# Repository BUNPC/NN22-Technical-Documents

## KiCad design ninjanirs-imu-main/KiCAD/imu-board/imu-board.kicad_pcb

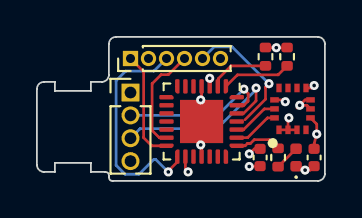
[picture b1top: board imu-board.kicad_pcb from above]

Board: 4 copper layers, 16.0 x 8.0 mm, 10 parts (0 on the bottom side), 14 nets.

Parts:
C1, C2: C_Small; C_0402_1005Metric
D1: LED; LED_0402_1005Metric
J1: Conn_01x04; PinHeader_1x04_P1.27mm_Vertical
J3: AVR-ISP-6; PinHeader_1x06_P1.00mm_Vertical
JP1, JP2: JPR2; R_0402_1005Metric
R1: R_US; R_0402_1005Metric
U2: ISM330DHCX; LGA-14L
U3: ATmega168A-MM; QFN-28-1EP_4x4mm_P0.45mm_EP2.4x2.4mm

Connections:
/MISO: J3.1 (MISO), U3.14 (PB4)
/MOSI: J3.4 (MOSI), U3.13 (PB3)
/RXD: J1.3, U3.26 (PD0)
/SCK: J3.3 (SCK), U3.15 (PB5)
/SCL: U2.P13 (SCL), U3.24 (PC5)
/SDA: U2.P14 (SDA/SDI/SDO), U3.23 (PC4)
/TXD: J1.2, U3.27 (PD1)
/nRESET: J3.5 (~RST), U3.25 (~RESET/PC6)
GND: C1.2, C2.2, D1.1 (K), J1.4, J3.6 (GND), JP1.2 (B), JP2.2 (B), U2.P1 (SDO/SA0), U2.P2 (SDX), U2.P3 (SCX), U2.P6 (GND@6), U2.P7 (GND@7), U3.4 (GND), U3.18 (GND), U3.29 (GND)
unnamed: D1.2 (A), R1.2
unnamed: JP1.1 (A), U3.2 (PD4)
unnamed: JP2.1 (A), U3.1 (PD3)
unnamed: R1.1, U3.22 (PC3)
VCC: C1.1, C2.1, J1.1, J3.2 (VCC), U2.P5 (VDD_IO), U2.P8 (VDD), U2.P12 (~CS), U3.3 (VCC), U3.16 (AVCC)

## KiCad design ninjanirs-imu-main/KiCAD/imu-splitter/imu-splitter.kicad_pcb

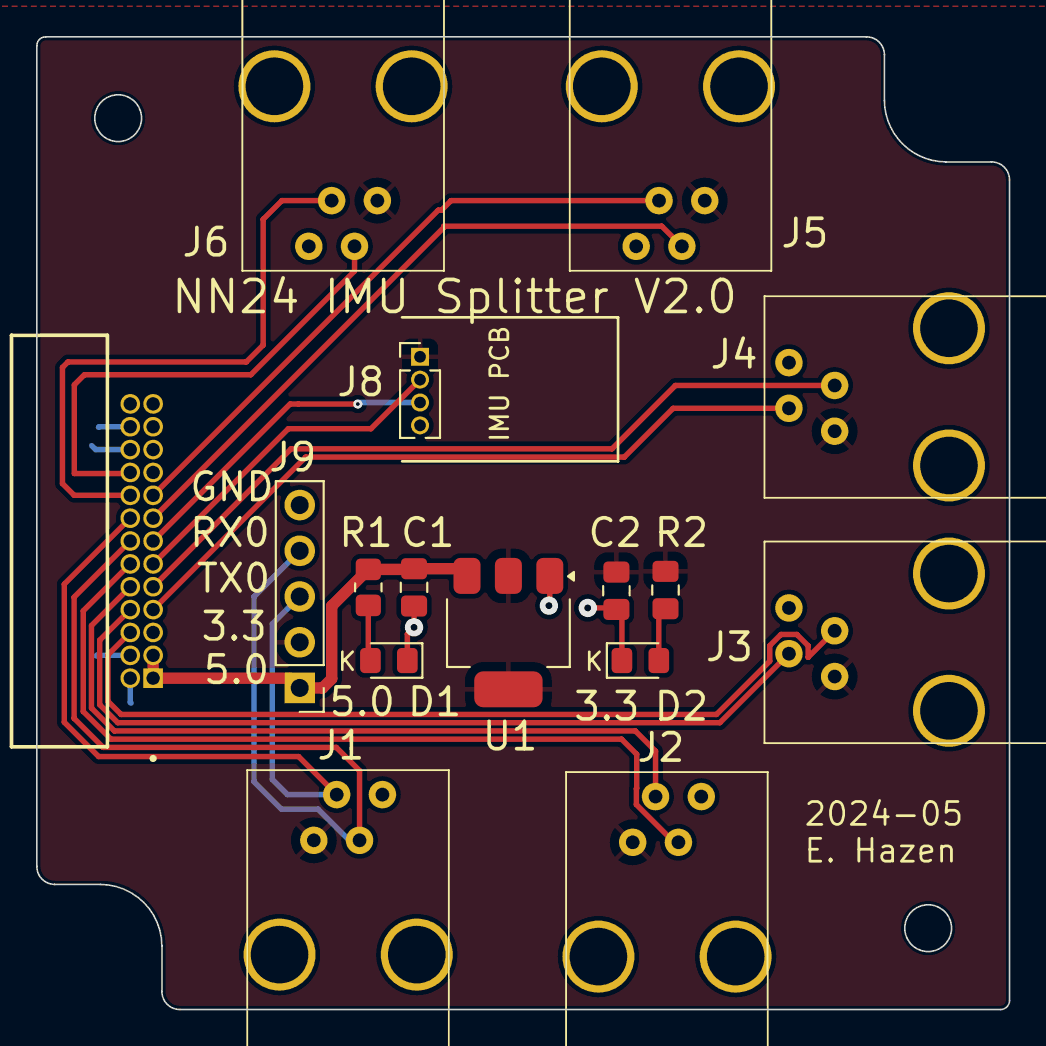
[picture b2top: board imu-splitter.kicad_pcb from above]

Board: 2 copper layers, 54.0 x 54.0 mm, 16 parts (0 on the bottom side), 19 nets.

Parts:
C1: 10uF; C_0805_2012Metric_Pad1.18x1.45mm_HandSolder
C2: 22uF; C_0805_2012Metric_Pad1.18x1.45mm_HandSolder
D1, D2: LED; LED_0805_2012Metric_Pad1.15x1.40mm_HandSolder
J1, J2, J3, J4, J5, J6: 4P4C; A-2004-3-4-LP
J7: 3220-26-0200-00; SAMTEC_SHF-113-01-L-D-RA
J8: Conn_01x04; PinHeader_1x04_P1.27mm_Vertical
J9: Conn_01x05; PinHeader_1x05_P2.54mm_Vertical
R1: 1.5k; R_0805_2012Metric_Pad1.20x1.40mm_HandSolder
R2: 510; C_0805_2012Metric_Pad1.18x1.45mm_HandSolder
U1: AP2114H-3.3TRG1; SOT-223-3_TabPin2

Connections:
+3.3V: C2.1, J1.1, J2.1, J3.1, J4.1, J5.1, J6.1, J8.1, J9.2, R2.1, U1.2 (VO)
+5V: C1.1, J7.1, J7.3, J9.1, R1.1, U1.3 (VI)
/RX0: J1.3, J7.14, J9.4
/RX1: J2.3, J7.12
/RX2: J3.3, J7.6
/RX3: J4.3, J7.9
/RX4: J5.3, J7.17
/RX5: J6.3, J7.18
/RX6: J7.13, J8.3
/TX0: J1.2, J7.16, J9.3
/TX1: J2.2, J7.10
/TX2: J3.2, J7.8
/TX3: J4.2, J7.7
/TX4: J5.2, J7.15
/TX5: J6.2, J7.20
/TX6: J7.11, J8.2
GND: C1.2, C2.2, D1.1 (K), D2.1 (K), J1.4, J2.4, J3.4, J4.4, J5.4, J6.4, J7.2, J7.4, J7.22, J7.24, J8.4, J9.5, U1.1 (GND)
unnamed: D1.2 (A), R1.2
unnamed: D2.2 (A), R2.2

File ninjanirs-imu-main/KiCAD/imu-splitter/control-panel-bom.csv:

"Reference","Value","Datasheet","Footprint","Qty","DNP"
"C1","10uF","~","Capacitor_SMD:C_0805_2012Metric_Pad1.18x1.45mm_HandSolder","1",""
"C2","22uF","~","Capacitor_SMD:C_0805_2012Metric_Pad1.18x1.45mm_HandSolder","1",""
"D1,D2","LED","~","LED_SMD:LED_0805_2012Metric_Pad1.15x1.40mm_HandSolder","2",""
"J1,J2,J3,J4,J5,J6","4P4C","~","my_RJ:A-2004-3-4-LP","6",""
"J7","3220-26-0200-00","~","models:SAMTEC_SHF-113-01-L-D-RA","1",""
"J8","Conn_01x04","~","Connector_PinHeader_1.27mm:PinHeader_1x04_P1.27mm_Vertical","1",""
"J9","Conn_01x05","~","Connector_PinHeader_2.54mm:PinHeader_1x05_P2.54mm_Vertical","1",""
"R1","1.5k","~","Resistor_SMD:R_0805_2012Metric_Pad1.20x1.40mm_HandSolder","1",""
"R2","510","~","Capacitor_SMD:C_0805_2012Metric_Pad1.18x1.45mm_HandSolder","1",""
"U1","AP2114H-3.3TRG1","https://www.diodes.com/assets/Datasheets/AZ1117.pdf","Package_TO_SOT_SMD:SOT-223-3_TabPin2","1",""

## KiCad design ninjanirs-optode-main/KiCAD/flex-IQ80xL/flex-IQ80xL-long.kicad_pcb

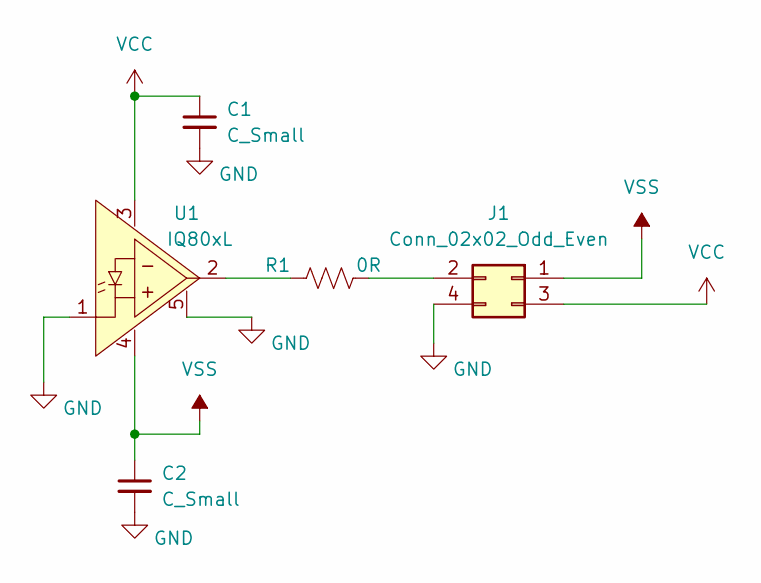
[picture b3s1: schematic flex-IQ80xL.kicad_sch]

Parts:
C1, C2: C_Small; C_0603_1608Metric
J1: Conn_02x02_Odd_Even; PinHeader_2x02_P1.27mm_compact
R1: 0R; R_0603_1608Metric
U1: IQ80xL

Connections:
GND: C1.2, C2.2, J1.4, U1.1 (GND), U1.5 (CASE)
unnamed: J1.2, R1.2
unnamed: R1.1, U1.2 (OUT)
VCC: C1.1, J1.3, U1.3 (V+)
VSS: C2.1, J1.1, U1.4 (V-)

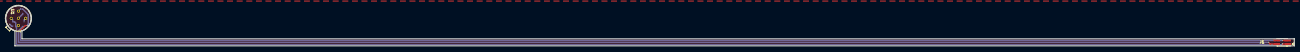
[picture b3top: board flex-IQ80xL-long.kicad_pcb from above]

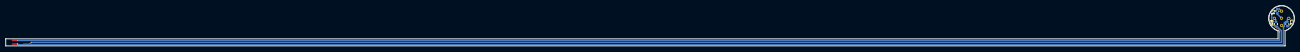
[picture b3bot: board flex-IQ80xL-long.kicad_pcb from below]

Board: 2 copper layers, 454.5 x 14.2 mm, 5 parts (3 on the bottom side), 5 nets.
